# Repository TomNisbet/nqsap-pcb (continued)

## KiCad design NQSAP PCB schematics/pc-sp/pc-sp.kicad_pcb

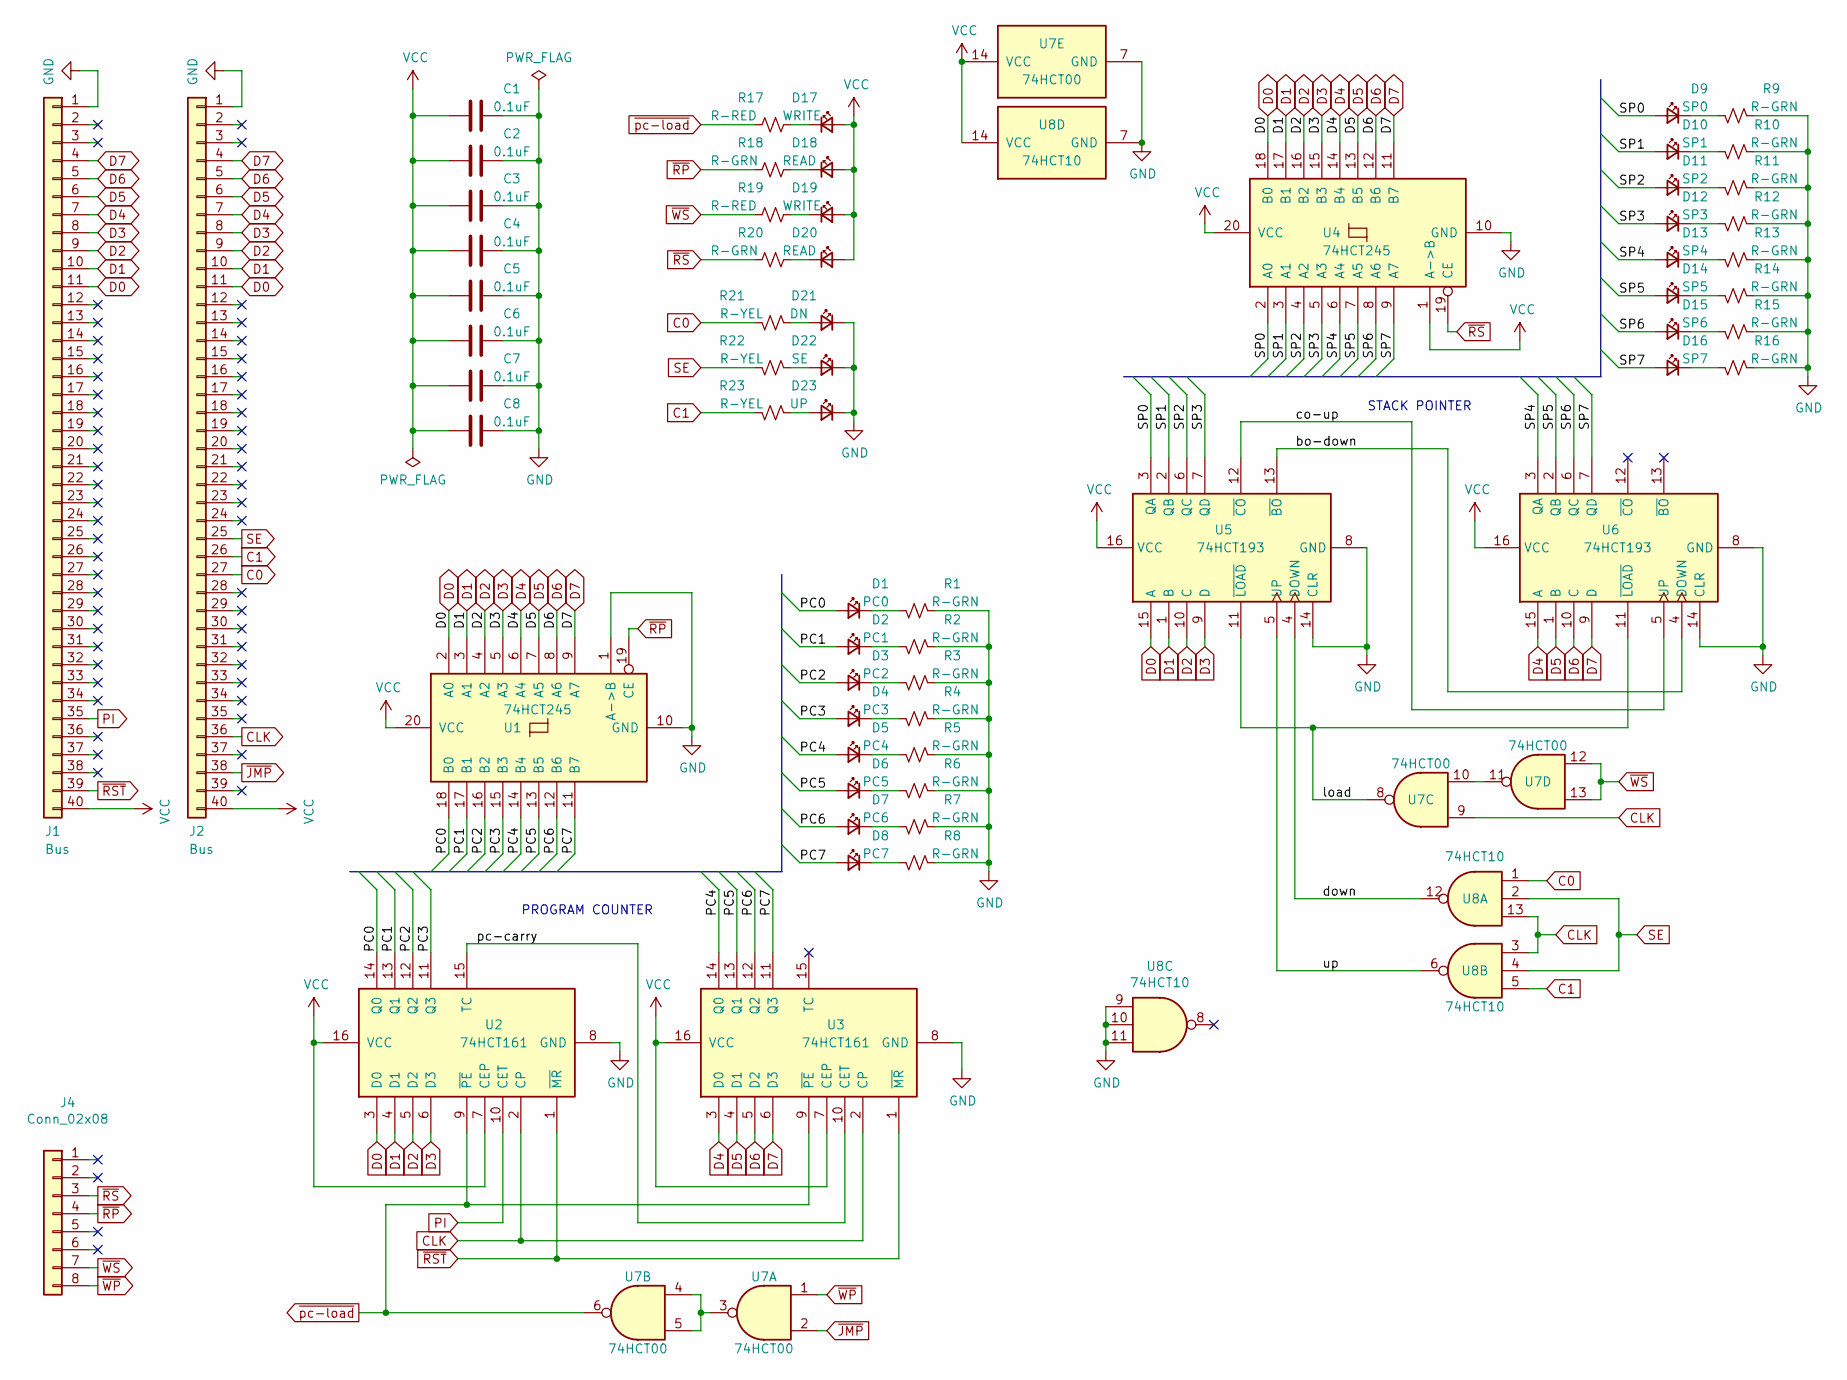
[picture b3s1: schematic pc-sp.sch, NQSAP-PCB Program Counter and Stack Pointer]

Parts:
C1, C2, C3, C4, C5, C6, C7, C8: 0.1uF; C_0805_2012Metric_Pad1.18x1.45mm_HandSolder
D1: PC0; LED_0805_2012Metric_Pad1.15x1.40mm_HandSolder
D2: PC1; LED_0805_2012Metric_Pad1.15x1.40mm_HandSolder
D3: PC2; LED_0805_2012Metric_Pad1.15x1.40mm_HandSolder
D4: PC3; LED_0805_2012Metric_Pad1.15x1.40mm_HandSolder
D5: PC4; LED_0805_2012Metric_Pad1.15x1.40mm_HandSolder
D6: PC5; LED_0805_2012Metric_Pad1.15x1.40mm_HandSolder
D7: PC6; LED_0805_2012Metric_Pad1.15x1.40mm_HandSolder
D8: PC7; LED_0805_2012Metric_Pad1.15x1.40mm_HandSolder
D9: SP0; LED_0805_2012Metric_Pad1.15x1.40mm_HandSolder
D10: SP1; LED_0805_2012Metric_Pad1.15x1.40mm_HandSolder
D11: SP2; LED_0805_2012Metric_Pad1.15x1.40mm_HandSolder
D12: SP3; LED_0805_2012Metric_Pad1.15x1.40mm_HandSolder
D13: SP4; LED_0805_2012Metric_Pad1.15x1.40mm_HandSolder
D14: SP5; LED_0805_2012Metric_Pad1.15x1.40mm_HandSolder
D15: SP6; LED_0805_2012Metric_Pad1.15x1.40mm_HandSolder
D16: SP7; LED_0805_2012Metric_Pad1.15x1.40mm_HandSolder
D17, D19: WRITE; LED_0805_2012Metric_Pad1.15x1.40mm_HandSolder
D18, D20: READ; LED_0805_2012Metric_Pad1.15x1.40mm_HandSolder
D21: DN; LED_0805_2012Metric_Pad1.15x1.40mm_HandSolder
D22: SE; LED_0805_2012Metric_Pad1.15x1.40mm_HandSolder
D23: UP; LED_0805_2012Metric_Pad1.15x1.40mm_HandSolder
J1, J2: Bus; PinHeader_1x40_P2.54mm_Vertical
J4: Conn_02x08; PinHeader_1x08_P2.54mm_Vertical
R1, R2, R3, R4, R5, R6, R7, R8, R9, R10, R11, R12, R13, R14, R15, R16, R18, R20: R-GRN; R_0805_2012Metric_Pad1.20x1.40mm_HandSolder
R17, R19: R-RED; R_0805_2012Metric_Pad1.20x1.40mm_HandSolder
R21, R22, R23: R-YEL; R_0805_2012Metric_Pad1.20x1.40mm_HandSolder
U1, U4: 74HCT245; DIP-20_W7.62mm
U2, U3: 74HCT161; DIP-16_W7.62mm
U5, U6: 74HCT193; DIP-16_W7.62mm
U7: 74HCT00; DIP-14_W7.62mm
U8: 74HCT10; DIP-14_W7.62mm

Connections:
/PC0: D1.2 (A), U1.18 (B0), U2.14 (Q0)
/PC1: D2.2 (A), U1.17 (B1), U2.13 (Q1)
/PC2: D3.2 (A), U1.16 (B2), U2.12 (Q2)
/PC3: D4.2 (A), U1.15 (B3), U2.11 (Q3)
/PC4: D5.2 (A), U1.14 (B4), U3.14 (Q0)
/PC5: D6.2 (A), U1.13 (B5), U3.13 (Q1)
/PC6: D7.2 (A), U1.12 (B6), U3.12 (Q2)
/PC7: D8.2 (A), U1.11 (B7), U3.11 (Q3)
/SP0: D9.2 (A), U4.2 (A0), U5.3 (QA)
/SP1: D10.2 (A), U4.3 (A1), U5.2 (QB)
/SP2: D11.2 (A), U4.4 (A2), U5.6 (QC)
/SP3: D12.2 (A), U4.5 (A3), U5.7 (QD)
/SP4: D13.2 (A), U4.6 (A4), U6.3 (QA)
/SP5: D14.2 (A), U4.7 (A5), U6.2 (QB)
/SP6: D15.2 (A), U4.8 (A6), U6.6 (QC)
/SP7: D16.2 (A), U4.9 (A7), U6.7 (QD)
/bo-down: U5.13 (~BO), U6.4 (DOWN)
/co-up: U5.12 (~CO), U6.5 (UP)
/down: U5.4 (DOWN), U8.12
/load: U5.11 (~LOAD), U6.11 (~LOAD), U7.8
/pc-carry: U2.15 (TC), U3.10 (CET)
/up: U5.5 (UP), U8.6
C0: J2.27, R21.1, U8.1
C1: J2.26, R23.1, U8.5
CLK: J2.36, U2.2 (CP), U3.2 (CP), U7.9, U8.3, U8.13
D0: J1.11, J2.11, U1.2 (A0), U2.3 (D0), U4.18 (B0), U5.15 (A)
D1: J1.10, J2.10, U1.3 (A1), U2.4 (D1), U4.17 (B1), U5.1 (B)
D2: J1.9, J2.9, U1.4 (A2), U2.5 (D2), U4.16 (B2), U5.10 (C)
D3: J1.8, J2.8, U1.5 (A3), U2.6 (D3), U4.15 (B3), U5.9 (D)
D4: J1.7, J2.7, U1.6 (A4), U3.3 (D0), U4.14 (B4), U6.15 (A)
D5: J1.6, J2.6, U1.7 (A5), U3.4 (D1), U4.13 (B5), U6.1 (B)
D6: J1.5, J2.5, U1.8 (A6), U3.5 (D2), U4.12 (B6), U6.10 (C)
D7: J1.4, J2.4, U1.9 (A7), U3.6 (D3), U4.11 (B7), U6.9 (D)
GND: C1.1, C2.1, C3.1, C4.1, C5.1, C6.1, C7.1, C8.1, D21.1 (K), D22.1 (K), D23.1 (K), J1.1, J2.1, R1.2, R2.2, R3.2, R4.2, R5.2, R6.2, R7.2, R8.2, R9.2, R10.2, R11.2, R12.2, R13.2, R14.2, R15.2, R16.2, U1.1 (A->B), U1.10 (GND), U2.8 (GND), U3.8 (GND), U4.10 (GND), U5.8 (GND), U5.14 (CLR), U6.8 (GND), U6.14 (CLR), U7.7 (GND), U8.7 (GND), U8.9, U8.10, U8.11
unnamed: D1.1 (K), R1.1
unnamed: D2.1 (K), R2.1
unnamed: D3.1 (K), R3.1
unnamed: D4.1 (K), R4.1
unnamed: D5.1 (K), R5.1
unnamed: D6.1 (K), R6.1
unnamed: D7.1 (K), R7.1
unnamed: D8.1 (K), R8.1
unnamed: D9.1 (K), R9.1
unnamed: D10.1 (K), R10.1
unnamed: D11.1 (K), R11.1
unnamed: D12.1 (K), R12.1
unnamed: D13.1 (K), R13.1
unnamed: D14.1 (K), R14.1
unnamed: D15.1 (K), R15.1
unnamed: D16.1 (K), R16.1
unnamed: D17.1 (K), R17.1
unnamed: D18.1 (K), R18.1
unnamed: D19.1 (K), R19.1
unnamed: D20.1 (K), R20.1
unnamed: D21.2 (A), R21.2
unnamed: D22.2 (A), R22.2
unnamed: D23.2 (A), R23.2
unnamed: U7.3, U7.4, U7.5
unnamed: U7.10, U7.11
PI: J1.35, U2.10 (CET)
SE: J2.25, R22.1, U8.2, U8.4
VCC: C1.2, C2.2, C3.2, C4.2, C5.2, C6.2, C7.2, C8.2, D17.2 (A), D18.2 (A), D19.2 (A), D20.2 (A), J1.40, J2.40, U1.20 (VCC), U2.7 (CEP), U2.16 (VCC), U3.7 (CEP), U3.16 (VCC), U4.1 (A->B), U4.20 (VCC), U5.16 (VCC), U6.16 (VCC), U7.14 (VCC), U8.14 (VCC)
~JMP: J2.38, U7.2
~RP: J4.4, R18.2, U1.19 (CE)
~RS: J4.3, R20.2, U4.19 (CE)
~RST: J1.39, U2.1 (~MR), U3.1 (~MR)
~WP: J4.8, U7.1
~WS: J4.7, R19.2, U7.12, U7.13
~pc-load: R17.2, U2.9 (~PE), U3.9 (~PE), U7.6

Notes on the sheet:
PROGRAM COUNTER
STACK POINTER

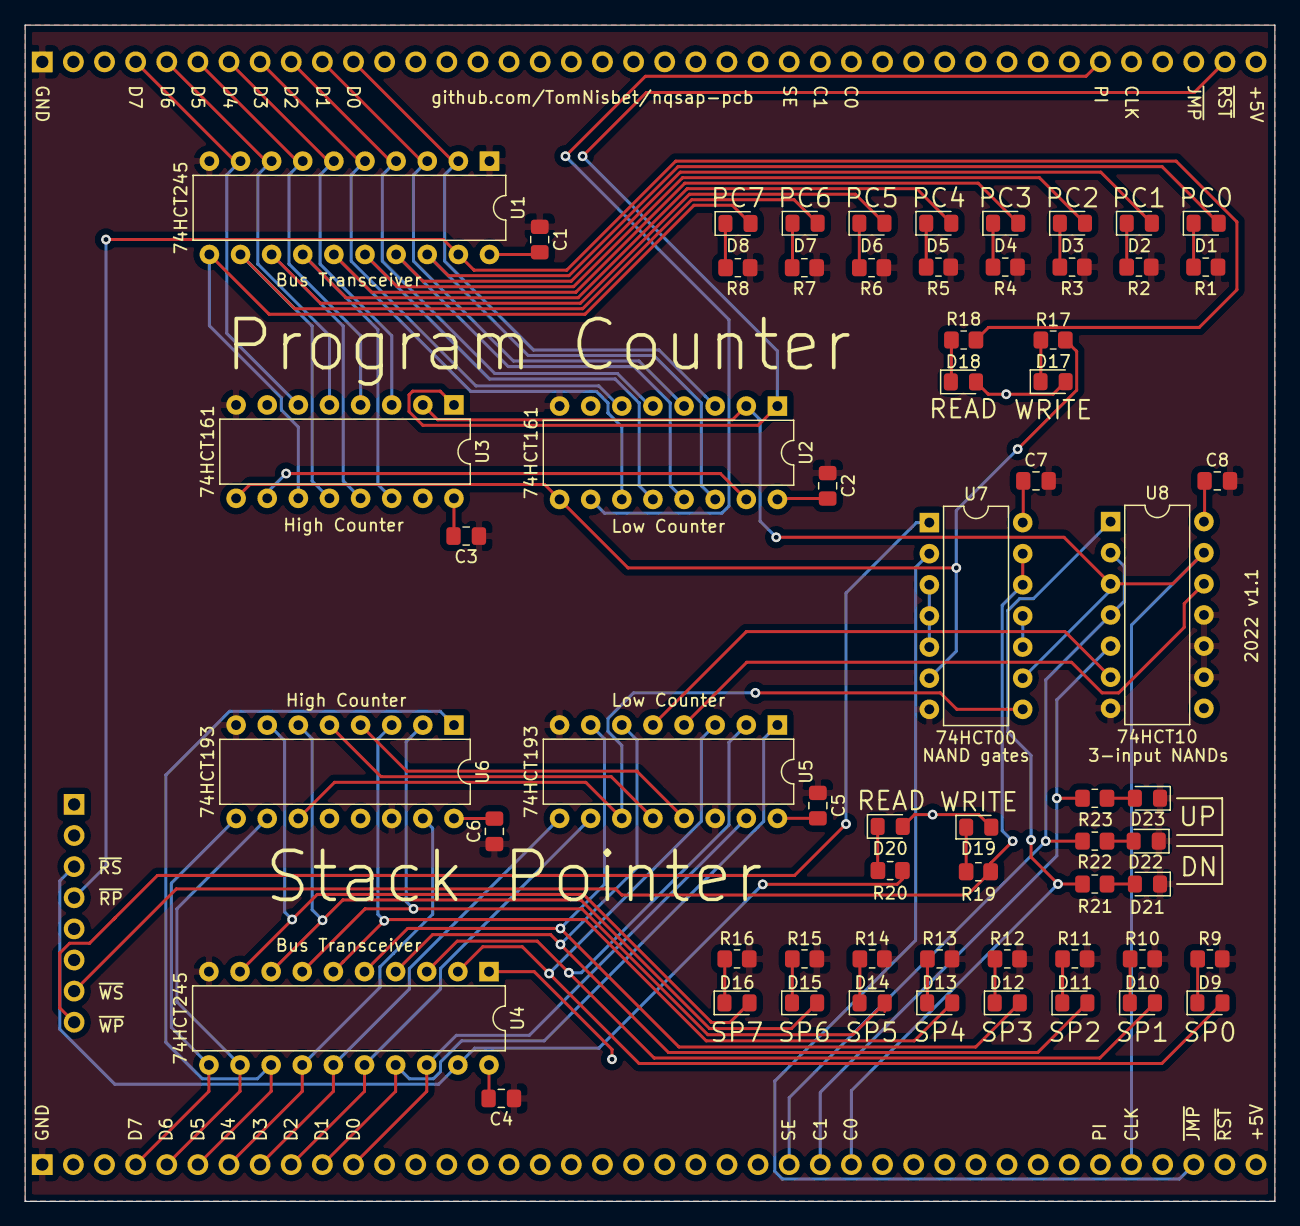
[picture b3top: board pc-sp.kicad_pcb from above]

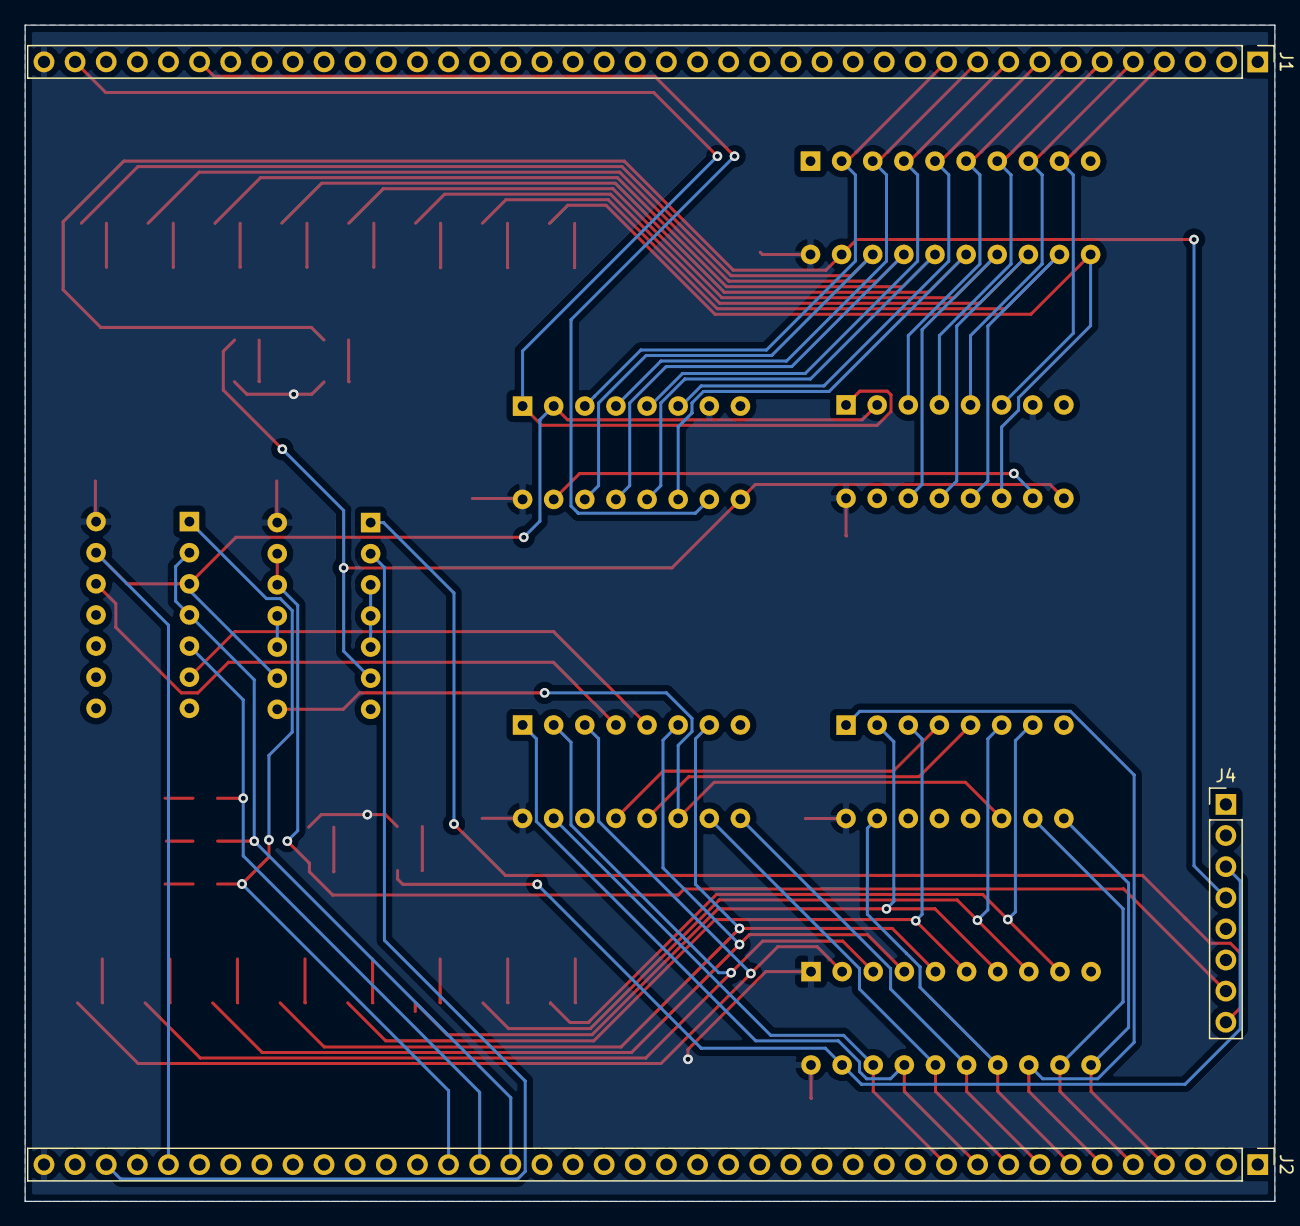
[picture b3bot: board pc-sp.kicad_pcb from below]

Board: 2 copper layers, 102.0 x 96.0 mm, 65 parts (3 on the bottom side), 69 nets.

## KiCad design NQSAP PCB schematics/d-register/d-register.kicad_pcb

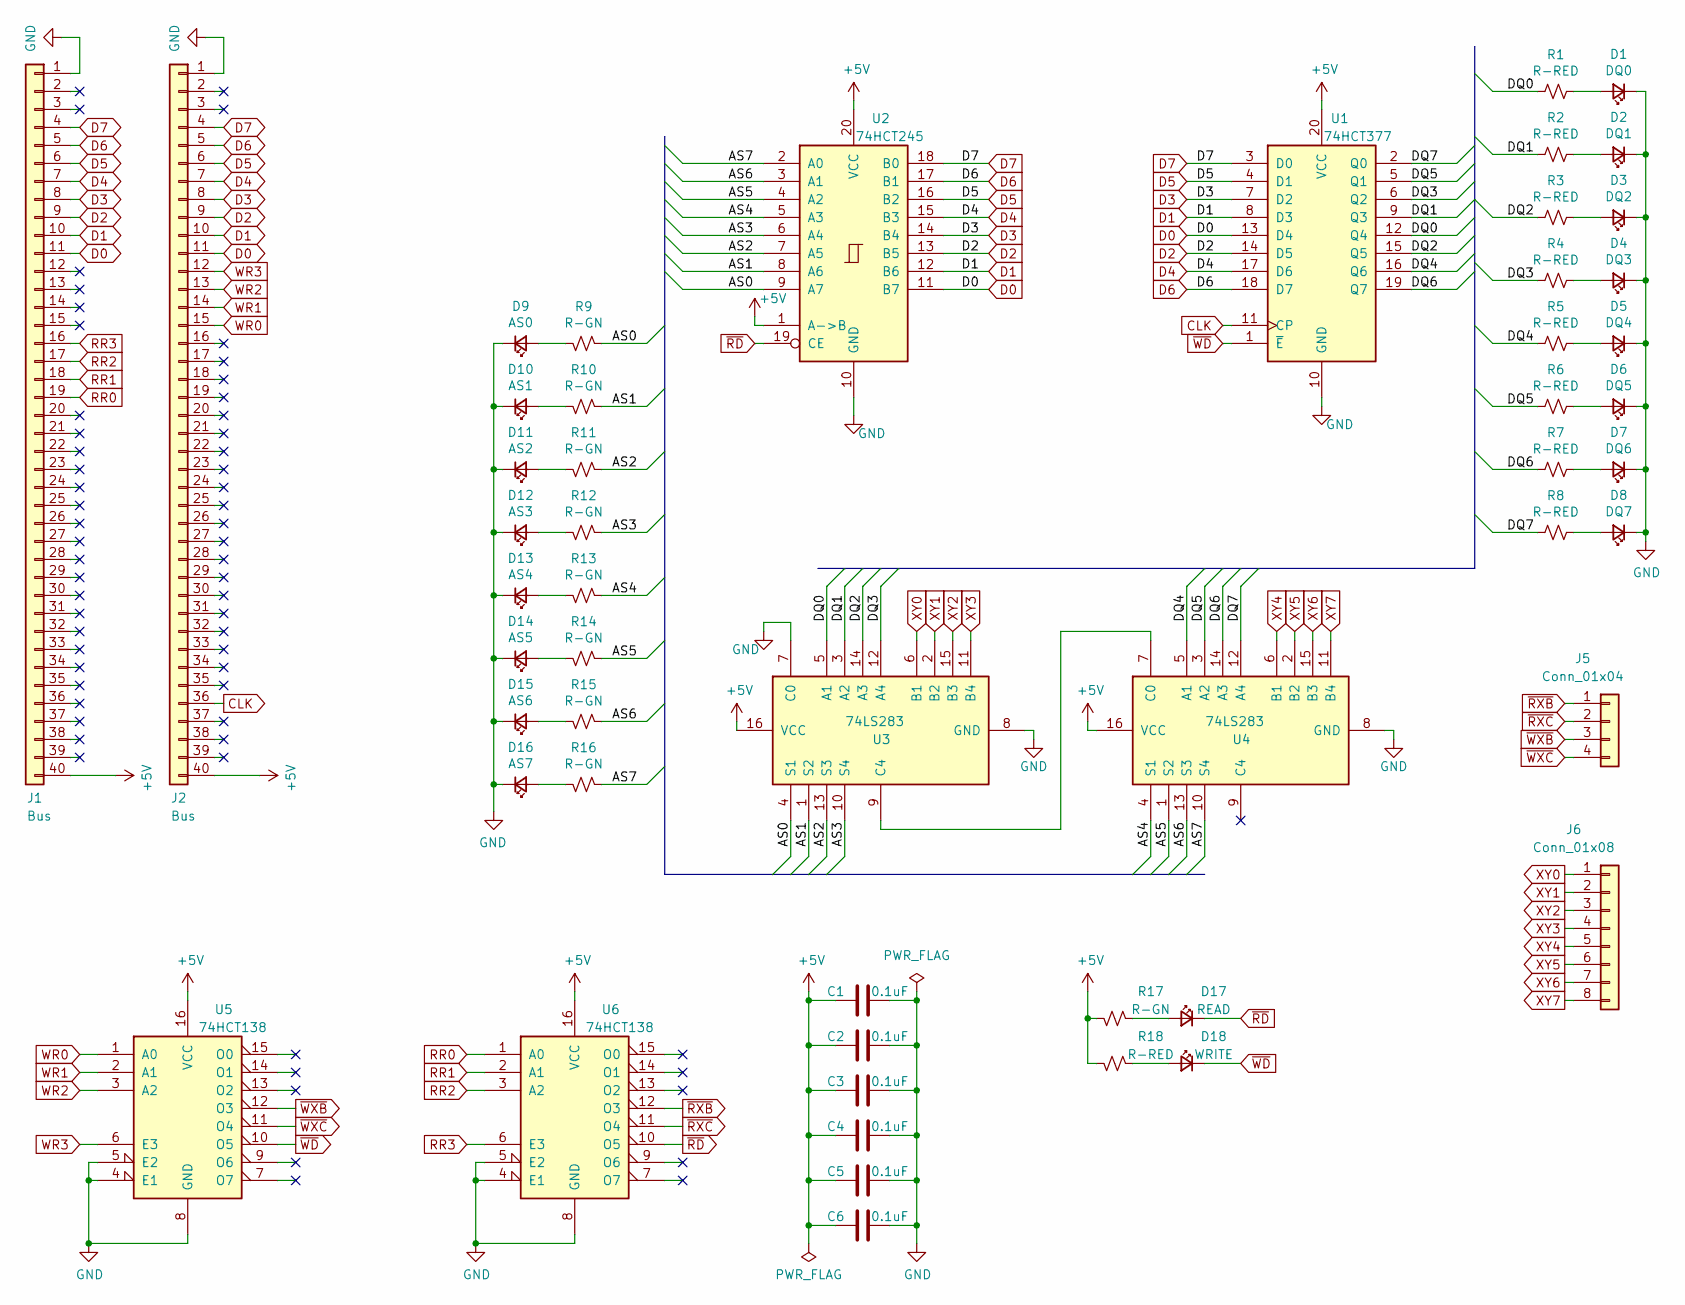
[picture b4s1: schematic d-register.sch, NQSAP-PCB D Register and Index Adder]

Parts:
C1, C2, C3, C4, C5, C6: 0.1uF; C_0805_2012Metric_Pad1.18x1.45mm_HandSolder
D1: DQ0; LED_0805_2012Metric_Pad1.15x1.40mm_HandSolder
D2: DQ1; LED_0805_2012Metric_Pad1.15x1.40mm_HandSolder
D3: DQ2; LED_0805_2012Metric_Pad1.15x1.40mm_HandSolder
D4: DQ3; LED_0805_2012Metric_Pad1.15x1.40mm_HandSolder
D5: DQ4; LED_0805_2012Metric_Pad1.15x1.40mm_HandSolder
D6: DQ5; LED_0805_2012Metric_Pad1.15x1.40mm_HandSolder
D7: DQ6; LED_0805_2012Metric_Pad1.15x1.40mm_HandSolder
D8: DQ7; LED_0805_2012Metric_Pad1.15x1.40mm_HandSolder
D9: AS0; LED_0805_2012Metric_Pad1.15x1.40mm_HandSolder
D10: AS1; LED_0805_2012Metric_Pad1.15x1.40mm_HandSolder
D11: AS2; LED_0805_2012Metric_Pad1.15x1.40mm_HandSolder
D12: AS3; LED_0805_2012Metric_Pad1.15x1.40mm_HandSolder
D13: AS4; LED_0805_2012Metric_Pad1.15x1.40mm_HandSolder
D14: AS5; LED_0805_2012Metric_Pad1.15x1.40mm_HandSolder
D15: AS6; LED_0805_2012Metric_Pad1.15x1.40mm_HandSolder
D16: AS7; LED_0805_2012Metric_Pad1.15x1.40mm_HandSolder
D17: READ; LED_0805_2012Metric_Pad1.15x1.40mm_HandSolder
D18: WRITE; LED_0805_2012Metric_Pad1.15x1.40mm_HandSolder
J1, J2: Bus; PinHeader_1x40_P2.54mm_Vertical
J5: Conn_01x04; PinHeader_1x04_P2.54mm_Vertical
J6: Conn_01x08; PinHeader_1x08_P2.54mm_Vertical
R1, R2, R3, R4, R5, R6, R7, R8, R18: R-RED; R_0805_2012Metric_Pad1.20x1.40mm_HandSolder
R9, R10, R11, R12, R13, R14, R15, R16, R17: R-GN; R_0805_2012Metric_Pad1.20x1.40mm_HandSolder
U1: 74HCT377; DIP-20_W7.62mm
U2: 74HCT245; DIP-20_W7.62mm
U3, U4: 74LS283; DIP-16_W7.62mm
U5, U6: 74HCT138; DIP-16_W7.62mm

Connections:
+5V: C1.2, C2.2, C3.2, C4.2, C5.2, C6.2, J1.40, J2.40, R17.1, R18.1, U1.20 (VCC), U2.1 (A->B), U2.20 (VCC), U3.16 (VCC), U4.16 (VCC), U5.16 (VCC), U6.16 (VCC)
/AS0: R9.2, U2.9 (A7), U3.4 (S1)
/AS1: R10.2, U2.8 (A6), U3.1 (S2)
/AS2: R11.2, U2.7 (A5), U3.13 (S3)
/AS3: R12.2, U2.6 (A4), U3.10 (S4)
/AS4: R13.2, U2.5 (A3), U4.4 (S1)
/AS5: R14.2, U2.4 (A2), U4.1 (S2)
/AS6: R15.2, U2.3 (A1), U4.13 (S3)
/AS7: R16.2, U2.2 (A0), U4.10 (S4)
/DQ0: R1.2, U1.12 (Q4), U3.5 (A1)
/DQ1: R2.2, U1.9 (Q3), U3.3 (A2)
/DQ2: R3.2, U1.15 (Q5), U3.14 (A3)
/DQ3: R4.2, U1.6 (Q2), U3.12 (A4)
/DQ4: R5.2, U1.16 (Q6), U4.5 (A1)
/DQ5: R6.2, U1.5 (Q1), U4.3 (A2)
/DQ6: R7.2, U1.19 (Q7), U4.14 (A3)
/DQ7: R8.2, U1.2 (Q0), U4.12 (A4)
CLK: J2.36, U1.11 (CP)
D0: J1.11, J2.11, U1.13 (D4), U2.11 (B7)
D1: J1.10, J2.10, U1.8 (D3), U2.12 (B6)
D2: J1.9, J2.9, U1.14 (D5), U2.13 (B5)
D3: J1.8, J2.8, U1.7 (D2), U2.14 (B4)
D4: J1.7, J2.7, U1.17 (D6), U2.15 (B3)
D5: J1.6, J2.6, U1.4 (D1), U2.16 (B2)
D6: J1.5, J2.5, U1.18 (D7), U2.17 (B1)
D7: J1.4, J2.4, U1.3 (D0), U2.18 (B0)
GND: C1.1, C2.1, C3.1, C4.1, C5.1, C6.1, D1.1 (K), D2.1 (K), D3.1 (K), D4.1 (K), D5.1 (K), D6.1 (K), D7.1 (K), D8.1 (K), D9.1 (K), D10.1 (K), D11.1 (K), D12.1 (K), D13.1 (K), D14.1 (K), D15.1 (K), D16.1 (K), J1.1, J2.1, U1.10 (GND), U2.10 (GND), U3.7 (C0), U3.8 (GND), U4.8 (GND), U5.4 (E1), U5.5 (E2), U5.8 (GND), U6.4 (E1), U6.5 (E2), U6.8 (GND)
unnamed: D1.2 (A), R1.1
unnamed: D2.2 (A), R2.1
unnamed: D3.2 (A), R3.1
unnamed: D4.2 (A), R4.1
unnamed: D5.2 (A), R5.1
unnamed: D6.2 (A), R6.1
unnamed: D7.2 (A), R7.1
unnamed: D8.2 (A), R8.1
unnamed: D9.2 (A), R9.1
unnamed: D10.2 (A), R10.1
unnamed: D11.2 (A), R11.1
unnamed: D12.2 (A), R12.1
unnamed: D13.2 (A), R13.1
unnamed: D14.2 (A), R14.1
unnamed: D15.2 (A), R15.1
unnamed: D16.2 (A), R16.1
unnamed: D17.2 (A), R17.2
unnamed: D18.2 (A), R18.2
unnamed: U3.9 (C4), U4.7 (C0)
RR0: J1.19, U6.1 (A0)
RR1: J1.18, U6.2 (A1)
RR2: J1.17, U6.3 (A2)
RR3: J1.16, U6.6 (E3)
WR0: J2.15, U5.1 (A0)
WR1: J2.14, U5.2 (A1)
WR2: J2.13, U5.3 (A2)
WR3: J2.12, U5.6 (E3)
XY0: J6.1, U3.6 (B1)
XY1: J6.2, U3.2 (B2)
XY2: J6.3, U3.15 (B3)
XY3: J6.4, U3.11 (B4)
XY4: J6.5, U4.6 (B1)
XY5: J6.6, U4.2 (B2)
XY6: J6.7, U4.15 (B3)
XY7: J6.8, U4.11 (B4)
~RD: D17.1 (K), U2.19 (CE), U6.10 (O5)
~RXB: J5.1, U6.12 (O3)
~RXC: J5.2, U6.11 (O4)
~WD: D18.1 (K), U1.1 (~E), U5.10 (O5)
~WXB: J5.3, U5.12 (O3)
~WXC: J5.4, U5.11 (O4)

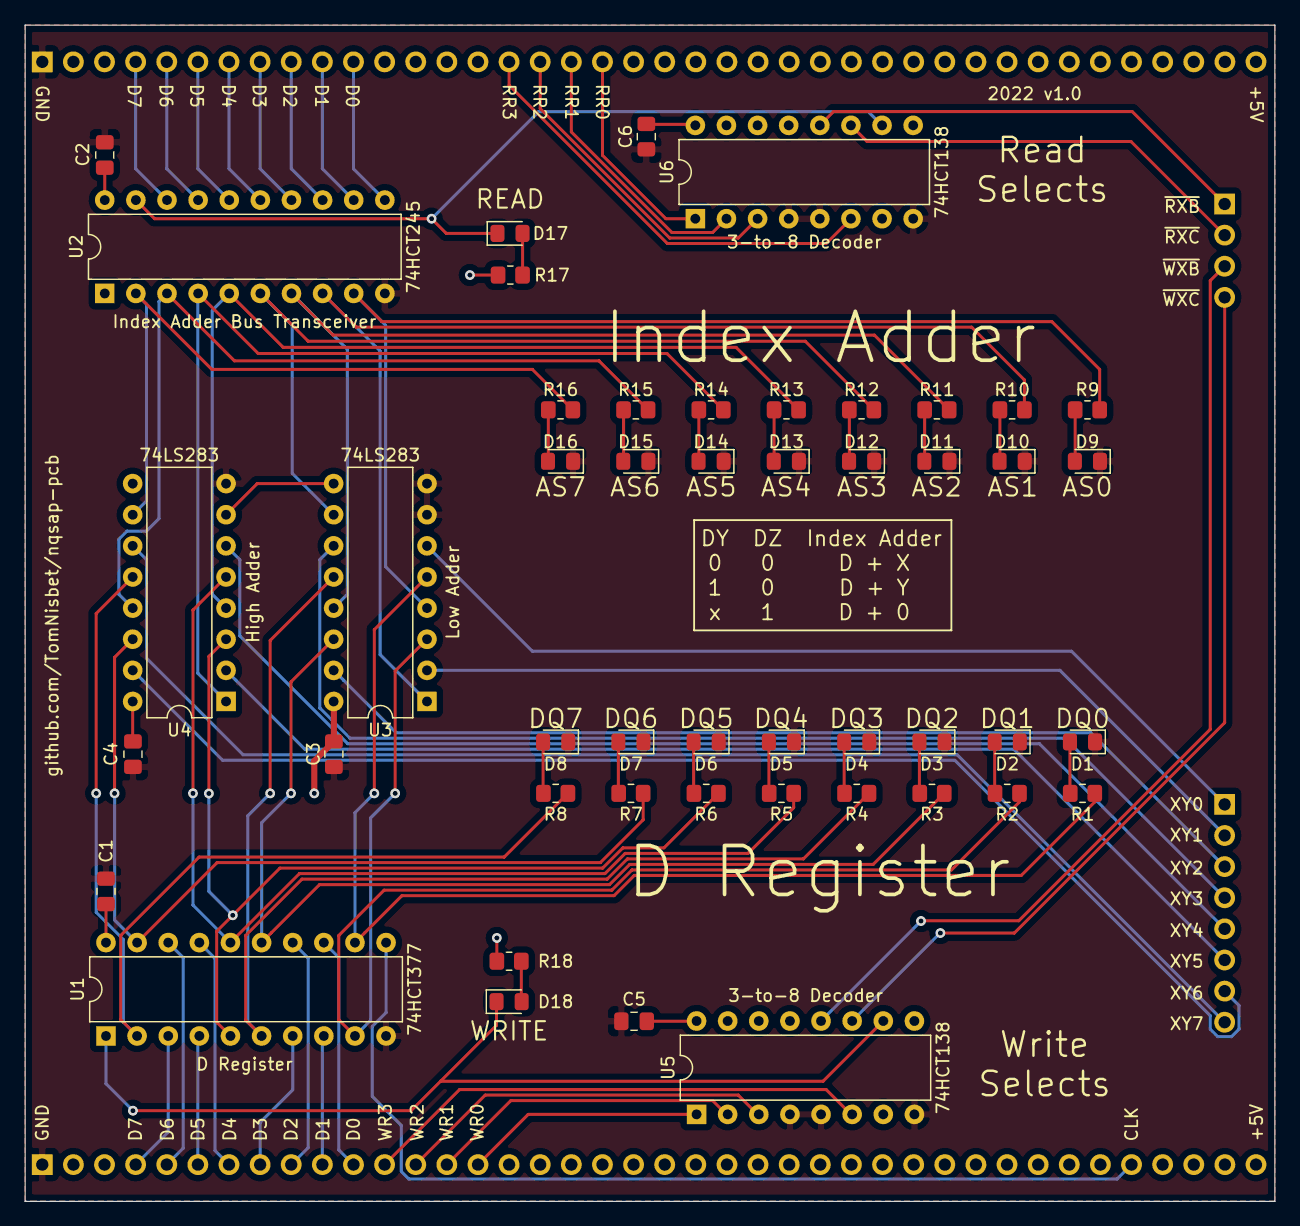
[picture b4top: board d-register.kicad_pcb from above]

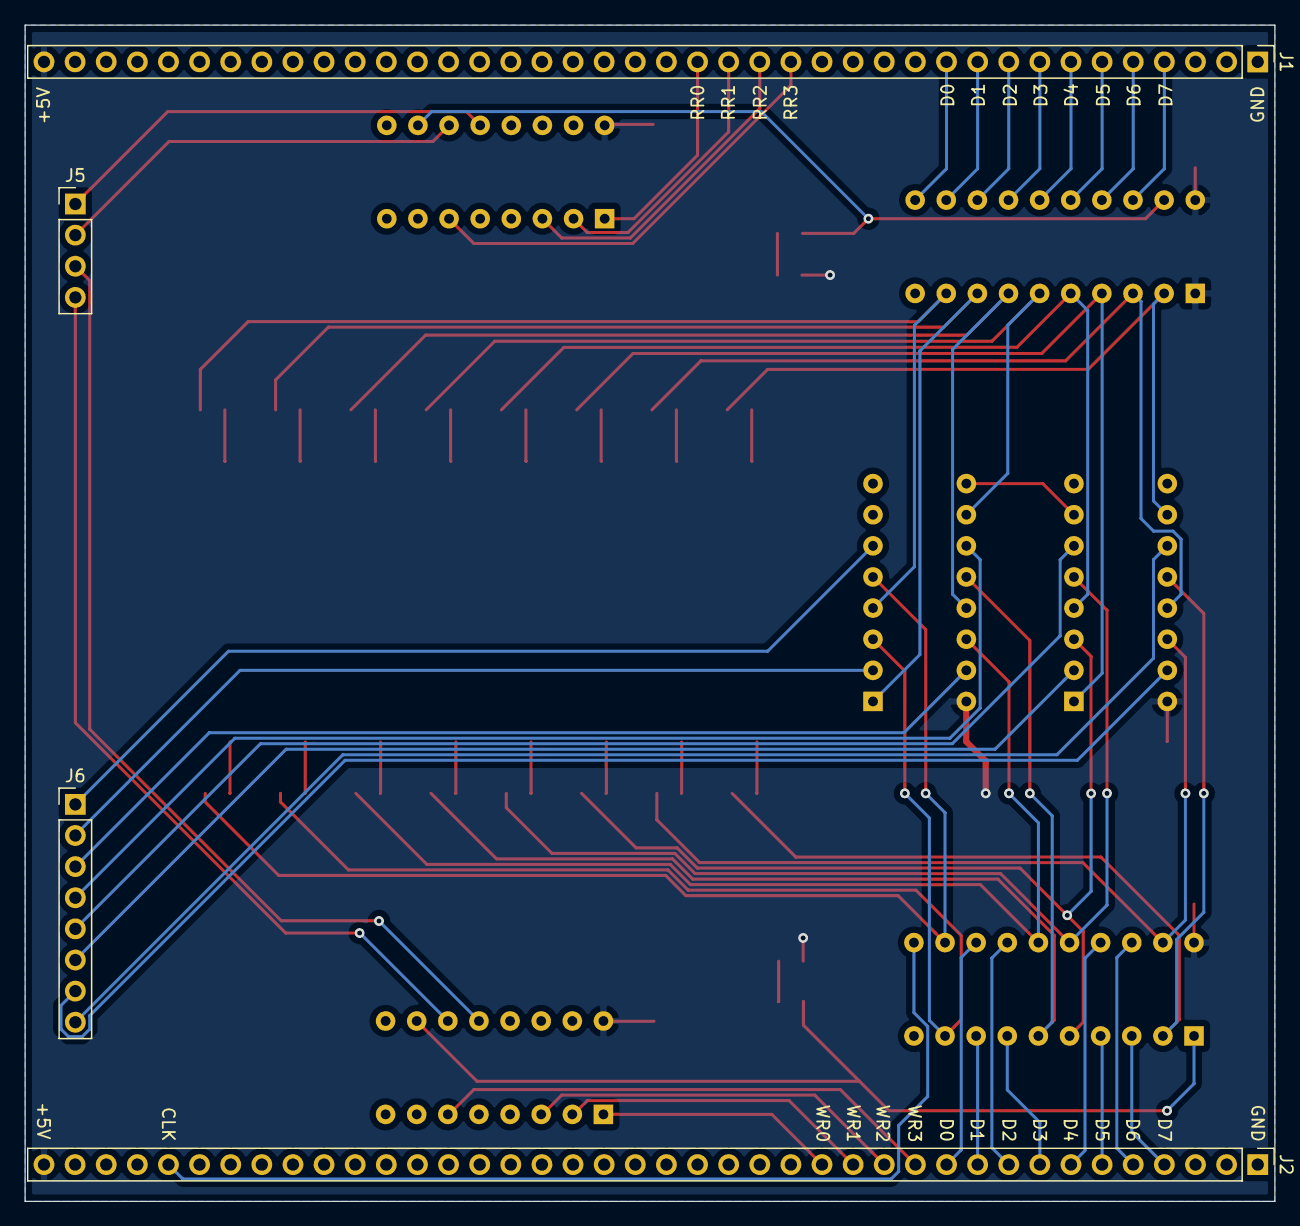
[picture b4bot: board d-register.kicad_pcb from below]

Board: 2 copper layers, 102.0 x 96.0 mm, 52 parts (4 on the bottom side), 68 nets.

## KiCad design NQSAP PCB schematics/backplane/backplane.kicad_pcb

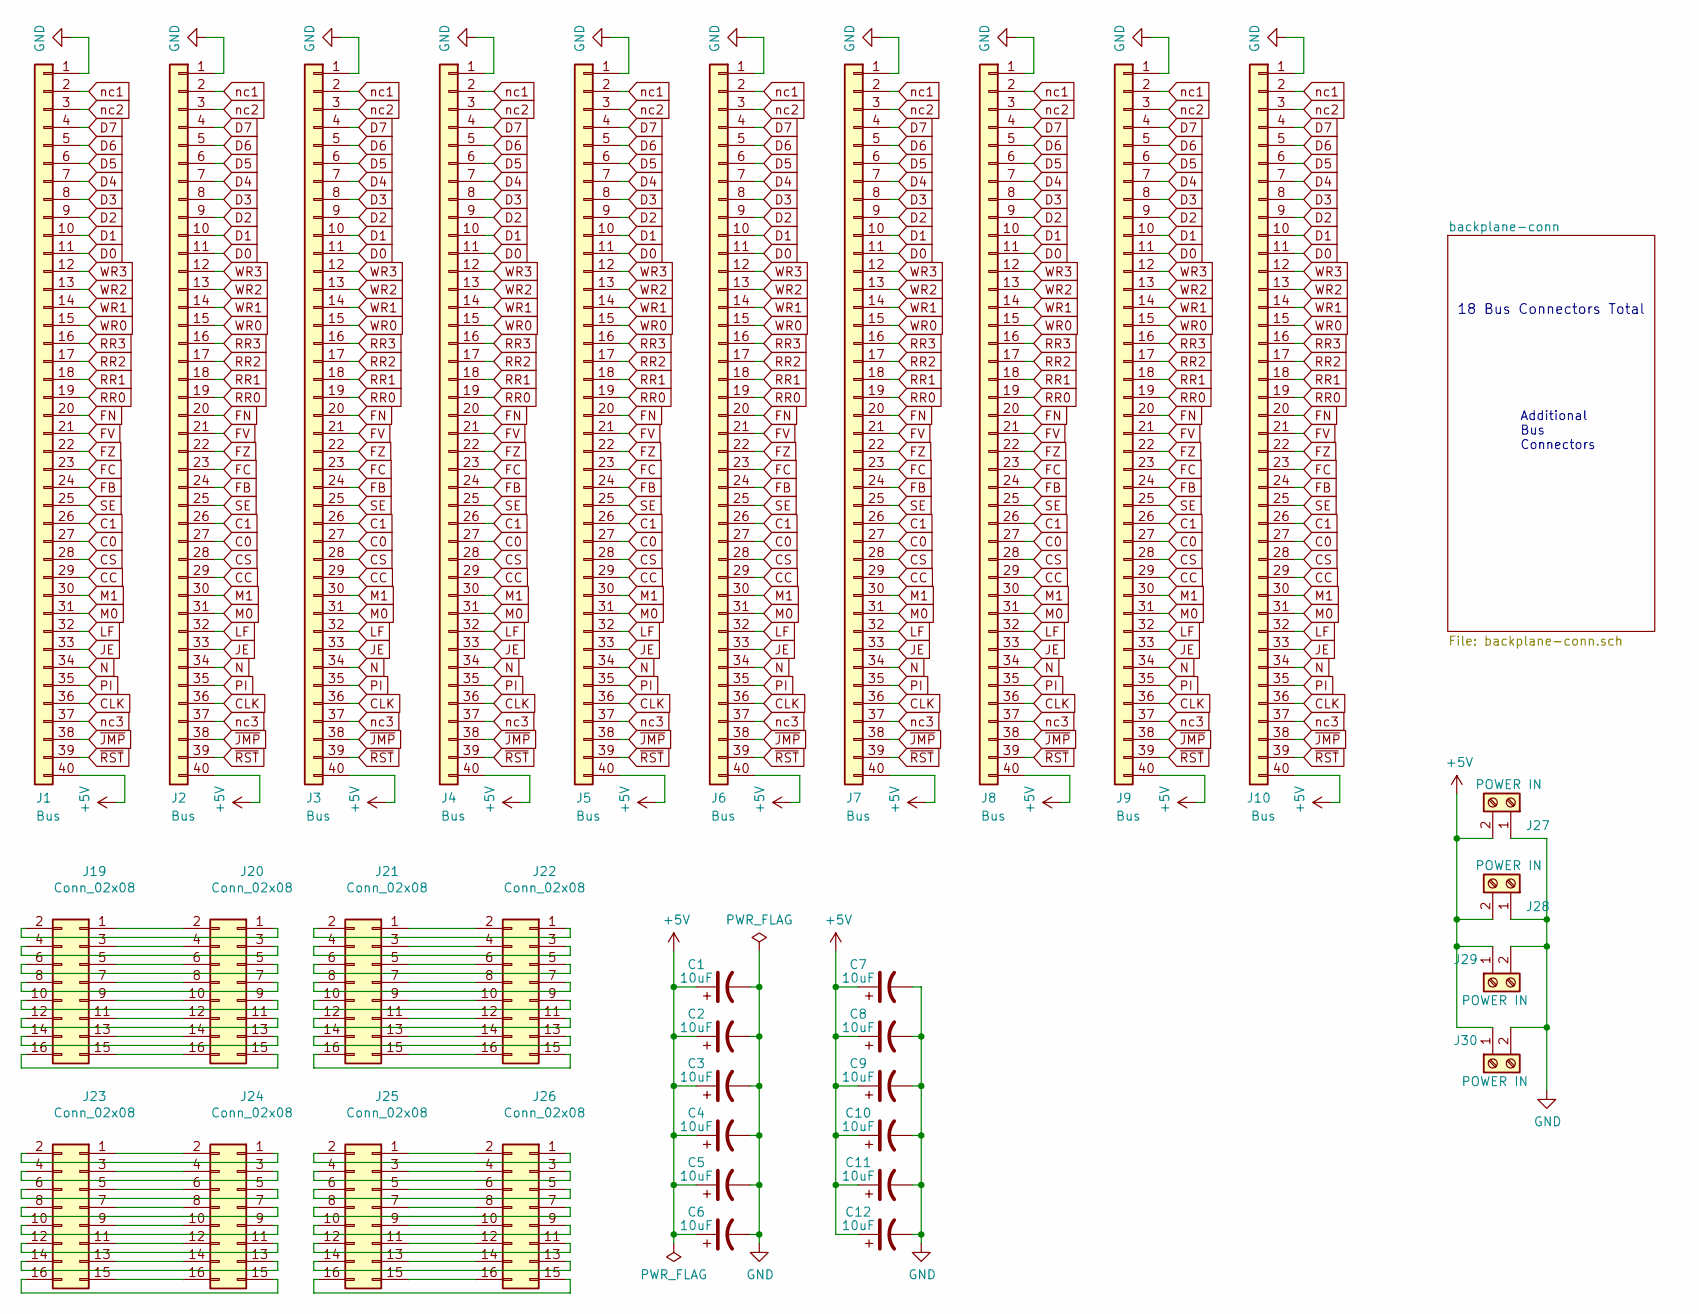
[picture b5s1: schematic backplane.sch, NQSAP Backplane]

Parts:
C1, C2, C3, C4, C5, C6, C7, C8, C9, C10, C11, C12: 10uF; C_Radial_D4.0mm_H5.0mm_P1.50mm
J1, J2, J3, J4, J5, J6, J7, J8, J9, J10: Bus; PinSocket_1x40_P2.54mm_Vertical
J19, J20, J21, J22, J23, J24, J25, J26: Conn_02x08; PinSocket_2x08_P2.54mm_Vertical
J27, J28, J29, J30: POWER IN; TerminalBlock_RND_205-00012_1x02_P5.00mm_Horizontal

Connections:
+5V: C1.1, C2.1, C3.1, C4.1, C5.1, C6.1, C7.1, C8.1, C9.1, C10.1, C11.1, C12.1, J1.40, J2.40, J3.40, J4.40, J5.40, J6.40, J7.40, J8.40, J9.40, J10.40, J27.2, J28.2, J29.1, J30.1; also elsewhere on the board
C0: J1.27, J2.27, J3.27, J4.27, J5.27, J6.27, J7.27, J8.27, J9.27, J10.27; also elsewhere on the board
C1: J1.26, J2.26, J3.26, J4.26, J5.26, J6.26, J7.26, J8.26, J9.26, J10.26; also elsewhere on the board
CC: J1.29, J2.29, J3.29, J4.29, J5.29, J6.29, J7.29, J8.29, J9.29, J10.29; also elsewhere on the board
CLK: J1.36, J2.36, J3.36, J4.36, J5.36, J6.36, J7.36, J8.36, J9.36, J10.36; also elsewhere on the board
CS: J1.28, J2.28, J3.28, J4.28, J5.28, J6.28, J7.28, J8.28, J9.28, J10.28; also elsewhere on the board
D0: J1.11, J2.11, J3.11, J4.11, J5.11, J6.11, J7.11, J8.11, J9.11, J10.11; also elsewhere on the board
D1: J1.10, J2.10, J3.10, J4.10, J5.10, J6.10, J7.10, J8.10, J9.10, J10.10; also elsewhere on the board
D2: J1.9, J2.9, J3.9, J4.9, J5.9, J6.9, J7.9, J8.9, J9.9, J10.9; also elsewhere on the board
D3: J1.8, J2.8, J3.8, J4.8, J5.8, J6.8, J7.8, J8.8, J9.8, J10.8; also elsewhere on the board
D4: J1.7, J2.7, J3.7, J4.7, J5.7, J6.7, J7.7, J8.7, J9.7, J10.7; also elsewhere on the board
D5: J1.6, J2.6, J3.6, J4.6, J5.6, J6.6, J7.6, J8.6, J9.6, J10.6; also elsewhere on the board
D6: J1.5, J2.5, J3.5, J4.5, J5.5, J6.5, J7.5, J8.5, J9.5, J10.5; also elsewhere on the board
D7: J1.4, J2.4, J3.4, J4.4, J5.4, J6.4, J7.4, J8.4, J9.4, J10.4; also elsewhere on the board
FB: J1.24, J2.24, J3.24, J4.24, J5.24, J6.24, J7.24, J8.24, J9.24, J10.24; also elsewhere on the board
FC: J1.23, J2.23, J3.23, J4.23, J5.23, J6.23, J7.23, J8.23, J9.23, J10.23; also elsewhere on the board
FN: J1.20, J2.20, J3.20, J4.20, J5.20, J6.20, J7.20, J8.20, J9.20, J10.20; also elsewhere on the board
FV: J1.21, J2.21, J3.21, J4.21, J5.21, J6.21, J7.21, J8.21, J9.21, J10.21; also elsewhere on the board
FZ: J1.22, J2.22, J3.22, J4.22, J5.22, J6.22, J7.22, J8.22, J9.22, J10.22; also elsewhere on the board
GND: C1.2, C2.2, C3.2, C4.2, C5.2, C6.2, C7.2, C8.2, C9.2, C10.2, C11.2, C12.2, J1.1, J2.1, J3.1, J4.1, J5.1, J6.1, J7.1, J8.1, J9.1, J10.1, J27.1, J28.1, J29.2, J30.2; also elsewhere on the board
JE: J1.33, J2.33, J3.33, J4.33, J5.33, J6.33, J7.33, J8.33, J9.33, J10.33; also elsewhere on the board
LF: J1.32, J2.32, J3.32, J4.32, J5.32, J6.32, J7.32, J8.32, J9.32, J10.32; also elsewhere on the board
M0: J1.31, J2.31, J3.31, J4.31, J5.31, J6.31, J7.31, J8.31, J9.31, J10.31; also elsewhere on the board
M1: J1.30, J2.30, J3.30, J4.30, J5.30, J6.30, J7.30, J8.30, J9.30, J10.30; also elsewhere on the board
N: J1.34, J2.34, J3.34, J4.34, J5.34, J6.34, J7.34, J8.34, J9.34, J10.34; also elsewhere on the board
unnamed: J19.1, J20.2
unnamed: J19.2, J20.1
unnamed: J19.3, J20.4
unnamed: J19.4, J20.3
unnamed: J19.5, J20.6
unnamed: J19.6, J20.5
unnamed: J19.7, J20.8
unnamed: J19.8, J20.7
unnamed: J19.9, J20.10
unnamed: J19.10, J20.9
unnamed: J19.11, J20.12
unnamed: J19.12, J20.11
unnamed: J19.13, J20.14
unnamed: J19.14, J20.13
unnamed: J19.15, J20.16
unnamed: J19.16, J20.15
unnamed: J21.1, J22.2
unnamed: J21.2, J22.1
unnamed: J21.3, J22.4
unnamed: J21.4, J22.3
unnamed: J21.5, J22.6
unnamed: J21.6, J22.5
unnamed: J21.7, J22.8
unnamed: J21.8, J22.7
unnamed: J21.9, J22.10
unnamed: J21.10, J22.9
unnamed: J21.11, J22.12
unnamed: J21.12, J22.11
unnamed: J21.13, J22.14
unnamed: J21.14, J22.13
unnamed: J21.15, J22.16
unnamed: J21.16, J22.15
unnamed: J23.1, J24.2
unnamed: J23.2, J24.1
unnamed: J23.3, J24.4
unnamed: J23.4, J24.3
unnamed: J23.5, J24.6
unnamed: J23.6, J24.5
unnamed: J23.7, J24.8
unnamed: J23.8, J24.7
unnamed: J23.9, J24.10
unnamed: J23.10, J24.9
unnamed: J23.11, J24.12
unnamed: J23.12, J24.11
unnamed: J23.13, J24.14
unnamed: J23.14, J24.13
unnamed: J23.15, J24.16
unnamed: J23.16, J24.15
unnamed: J25.1, J26.2
unnamed: J25.2, J26.1
unnamed: J25.3, J26.4
unnamed: J25.4, J26.3
unnamed: J25.5, J26.6
unnamed: J25.6, J26.5
unnamed: J25.7, J26.8
unnamed: J25.8, J26.7
unnamed: J25.9, J26.10
unnamed: J25.10, J26.9
unnamed: J25.11, J26.12
unnamed: J25.12, J26.11
unnamed: J25.13, J26.14
unnamed: J25.14, J26.13
unnamed: J25.15, J26.16
unnamed: J25.16, J26.15
PI: J1.35, J2.35, J3.35, J4.35, J5.35, J6.35, J7.35, J8.35, J9.35, J10.35; also elsewhere on the board
RR0: J1.19, J2.19, J3.19, J4.19, J5.19, J6.19, J7.19, J8.19, J9.19, J10.19; also elsewhere on the board
RR1: J1.18, J2.18, J3.18, J4.18, J5.18, J6.18, J7.18, J8.18, J9.18, J10.18; also elsewhere on the board
RR2: J1.17, J2.17, J3.17, J4.17, J5.17, J6.17, J7.17, J8.17, J9.17, J10.17; also elsewhere on the board
RR3: J1.16, J2.16, J3.16, J4.16, J5.16, J6.16, J7.16, J8.16, J9.16, J10.16; also elsewhere on the board
SE: J1.25, J2.25, J3.25, J4.25, J5.25, J6.25, J7.25, J8.25, J9.25, J10.25; also elsewhere on the board
WR0: J1.15, J2.15, J3.15, J4.15, J5.15, J6.15, J7.15, J8.15, J9.15, J10.15; also elsewhere on the board
WR1: J1.14, J2.14, J3.14, J4.14, J5.14, J6.14, J7.14, J8.14, J9.14, J10.14; also elsewhere on the board
WR2: J1.13, J2.13, J3.13, J4.13, J5.13, J6.13, J7.13, J8.13, J9.13, J10.13; also elsewhere on the board
WR3: J1.12, J2.12, J3.12, J4.12, J5.12, J6.12, J7.12, J8.12, J9.12, J10.12; also elsewhere on the board
nc1: J1.2, J2.2, J3.2, J4.2, J5.2, J6.2, J7.2, J8.2, J9.2, J10.2; also elsewhere on the board
nc2: J1.3, J2.3, J3.3, J4.3, J5.3, J6.3, J7.3, J8.3, J9.3, J10.3; also elsewhere on the board
nc3: J1.37, J2.37, J3.37, J4.37, J5.37, J6.37, J7.37, J8.37, J9.37, J10.37; also elsewhere on the board
~JMP: J1.38, J2.38, J3.38, J4.38, J5.38, J6.38, J7.38, J8.38, J9.38, J10.38; also elsewhere on the board
~RST: J1.39, J2.39, J3.39, J4.39, J5.39, J6.39, J7.39, J8.39, J9.39, J10.39; also elsewhere on the board

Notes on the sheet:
Additional Bus Connectors
18 Bus Connectors Total
